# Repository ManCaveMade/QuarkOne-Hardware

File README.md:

# QuarkOne - Hardware
Designed by: Mitchell A. Cox (20 Febrary 2016) (ManCave Made)

Copyright: Mitchell A. Cox (mitch [at] enox [dot] co [dot] za)

License: CERN OHL v1.2

The hardware design files for the Quark One. The free version of eagle is sufficient to open, modify and use the Quark One design files. PDFs are provided for convenience.

The board uses two layers for minimum cost. The Atmel XMEGA microcontroller footprint is compatible with any similar device with different flash size, for example.

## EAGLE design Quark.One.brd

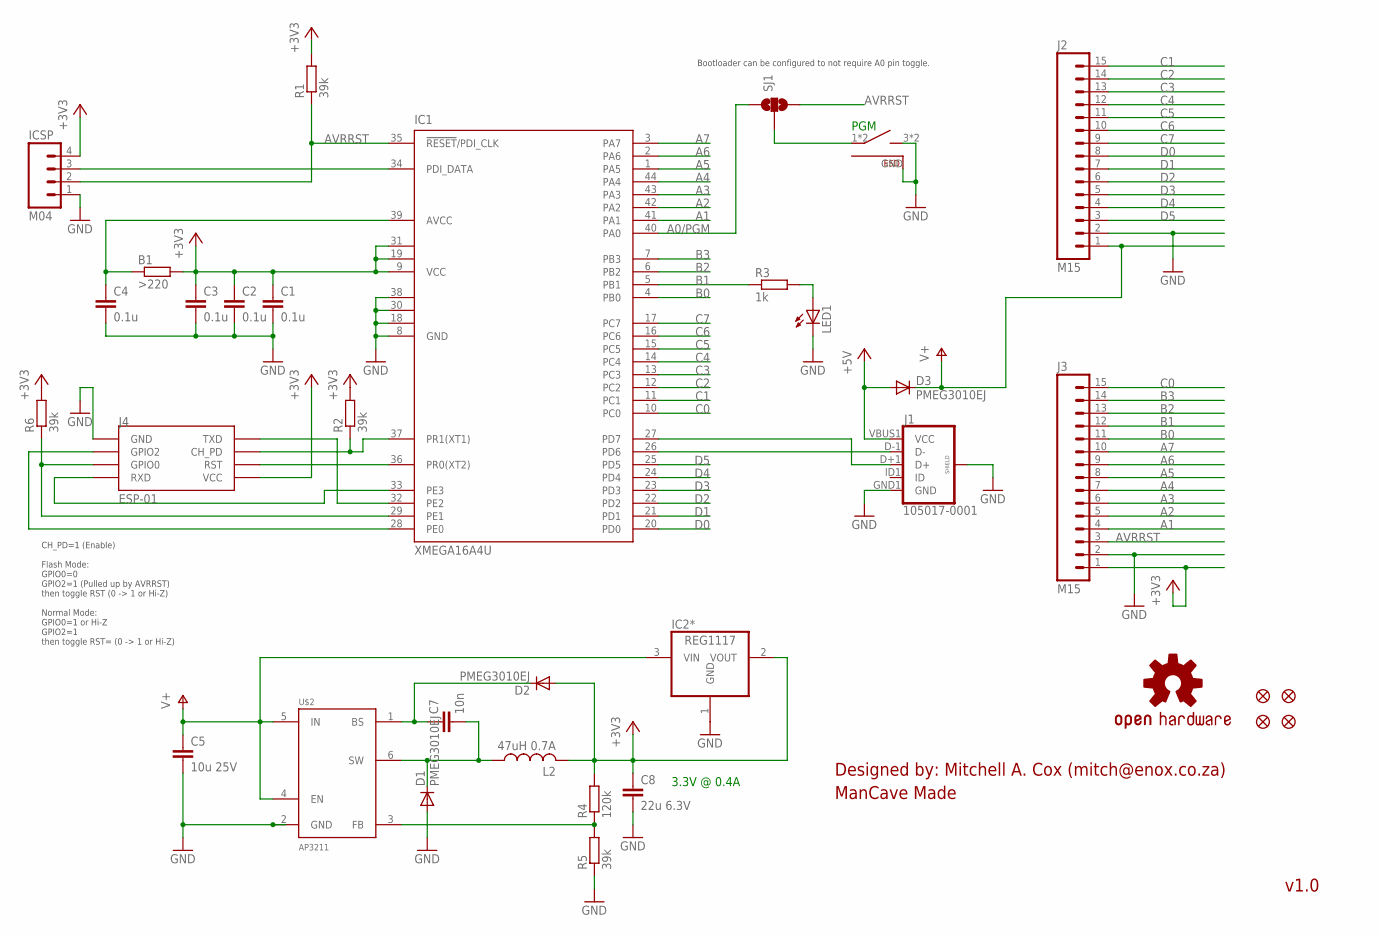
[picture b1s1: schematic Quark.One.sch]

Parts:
B1: >220; R0603
C1, C2, C3, C4: 0.1u; C0603
C5: 10u 25V; C0805
C7: 10n; C0603
C8: 22u 6.3V; C0805
D1, D2, D3: PMEG3010EJ; SOD-323
IC1: XMEGA16A4U; TQFP44
IC2*: REG1117; SOT223
ICSP: M04; 1X04-LOCK
J1: 105017-0001; USB-MICROB
J2, J3: M15; 1X15
J4: ESP-01; ESP01
JP1, JP2, JP3, JP4: FIDUCIALUFIDUCIAL; MICRO-FIDUCIAL
L2: 47uH 0.7A; LQH44P
LED1: LEDCHIPLED_0603; CHIPLED_0603
R1, R2, R5, R6: 39k; R0603
R3: 1k; R0603
R4: 120k; R0603
S1: PTS840; PTS840-SW
SJ1: SOLDERJUMPER_2WAY-OLDPASTE2&3; SJ_3_PASTE2&3
U$1: OSHW; OSHW-S
U$2: AP3211; SOT23-6

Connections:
+3V3: B1.2, C1.1, C2.1, C3.1, C8.1, D2.2 (A), IC1.9 (VCC), IC1.19 (VCC1), IC1.31 (VCC2), IC2*.2 (VOUT), ICSP.4, J3.1, J4.VCC, L2.2, R1.2, R2.2, R4.2, R6.2
+5V: D3.2 (A), J1.VBUS1 (VCC)
A0/PGM: IC1.40 (PA0), SJ1.1
A1: IC1.41 (PA1), J3.4
A2: IC1.42 (PA2), J3.5
A3: IC1.43 (PA3), J3.6
A4: IC1.44 (PA4), J3.7
A5: IC1.1 (PA5), J3.8
A6: IC1.2 (PA6), J3.9
A7: IC1.3 (PA7), J3.10
AVRRST: IC1.35 (!RESET!/PDI_CLK), ICSP.2, J3.3, R1.1, SJ1.3
B0: IC1.4 (PB0), J3.11
B1: IC1.5 (PB1), J3.12, R3.1
B2: IC1.6 (PB2), J3.13
B3: IC1.7 (PB3), J3.14
C0: IC1.10 (PC0), J3.15
C1: IC1.11 (PC1), J2.15
C2: IC1.12 (PC2), J2.14
C3: IC1.13 (PC3), J2.13
C4: IC1.14 (PC4), J2.12
C5: IC1.15 (PC5), J2.11
C6: IC1.16 (PC6), J2.10
C7: IC1.17 (PC7), J2.9
D0: IC1.20 (PD0), J2.8
D1: IC1.21 (PD1), J2.7
D2: IC1.22 (PD2), J2.6
D3: IC1.23 (PD3), J2.5
D4: IC1.24 (PD4), J2.4
D5: IC1.25 (PD5), J2.3
GND: C1.2, C2.2, C3.2, C4.2, C5.2, C8.2, D1.2 (A), IC1.8 (GND), IC1.18 (GND1), IC1.30 (GND2), IC1.38 (GND3), IC2*.1 (GND), ICSP.1, J1.GND1 (GND), J1.P$1 (SHIELD), J1.P$2 (SHIELD), J1.P$7 (SHIELD), J1.P$8 (SHIELD), J1.SHIELD, J1.SHIELD2 (SHIELD), J2.2, J3.2, J4.GND, LED1.C, R5.1, S1.3, S1.4, S1.GND, U$2.2 (GND)
unnamed: LED1.A, R3.2
unnamed: IC1.32 (PE2), J4.TX (TXD)
unnamed: C7.2, D1.1 (C), L2.1, U$2.6 (SW)
unnamed: IC1.34 (PDI_DATA), ICSP.3
unnamed: B1.1, C4.1, IC1.39 (AVCC)
unnamed: R4.1, R5.2, U$2.3 (FB)
unnamed: IC1.33 (PE3), J4.RX (RXD)
unnamed: IC1.26 (PD6), J1.D-1 (D-)
unnamed: IC1.27 (PD7), J1.D+1 (D+)
unnamed: C7.1, D2.1 (C), U$2.1 (BS)
unnamed: IC1.37 (PR1(XT1)), J4.CH_PD, R2.1
unnamed: IC1.36 (PR0(XT2)), J4.RST
unnamed: IC1.28 (PE0), J4.GPIO2
unnamed: IC1.29 (PE1), J4.GPIO0, R6.1
unnamed: S1.1, S1.2, SJ1.2
V+: C5.1, D3.1 (C), IC2*.3 (VIN), J2.1, U$2.4 (EN), U$2.5 (IN)

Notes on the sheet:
3.3V @ 0.4A
PGM
CH_PD=1 (Enable) Flash Mode: GPIO0=0 GPIO2=1 (Pulled up by AVRRST) then toggle RST (0 -> 1 or Hi-Z) Normal Mode: GPIO0=1 or Hi-Z GPIO2=1 then toggle RST= (0 -> 1 or Hi-Z)
Bootloader can be configured to not require A0 pin toggle.
v1.0
Designed by: Mitchell A. Cox (mitch@enox.co.za) ManCave Made

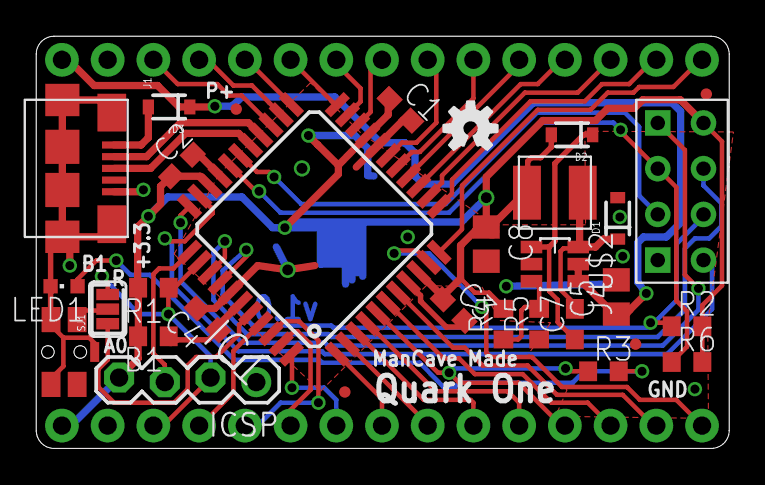
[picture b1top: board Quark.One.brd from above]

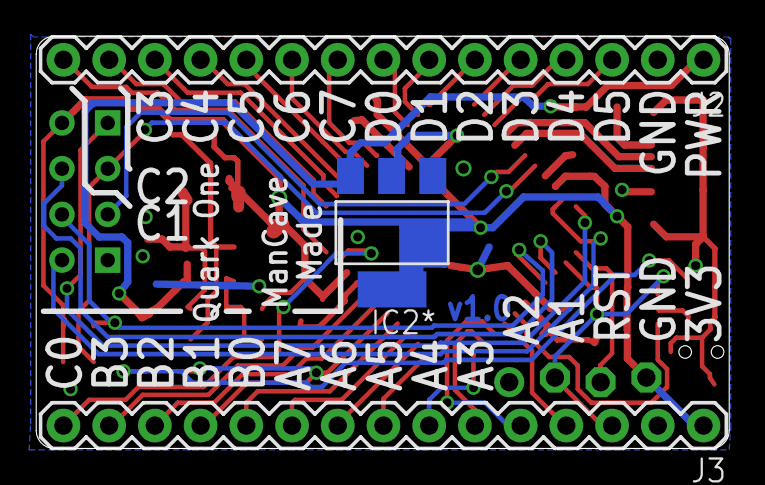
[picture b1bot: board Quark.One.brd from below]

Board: 2 copper layers, 38.5 x 22.9 mm, 34 parts (3 on the bottom side), 46 nets.

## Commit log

2016-02-20 Added Cadsoft Eagle 7.3.0 design files
2016-02-20 Added schematic PDF

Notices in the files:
parts and their libraries:
SparkFun: Licensing: CC v3.0 Share-Alike You are welcome to use this library for commercial purposes.
